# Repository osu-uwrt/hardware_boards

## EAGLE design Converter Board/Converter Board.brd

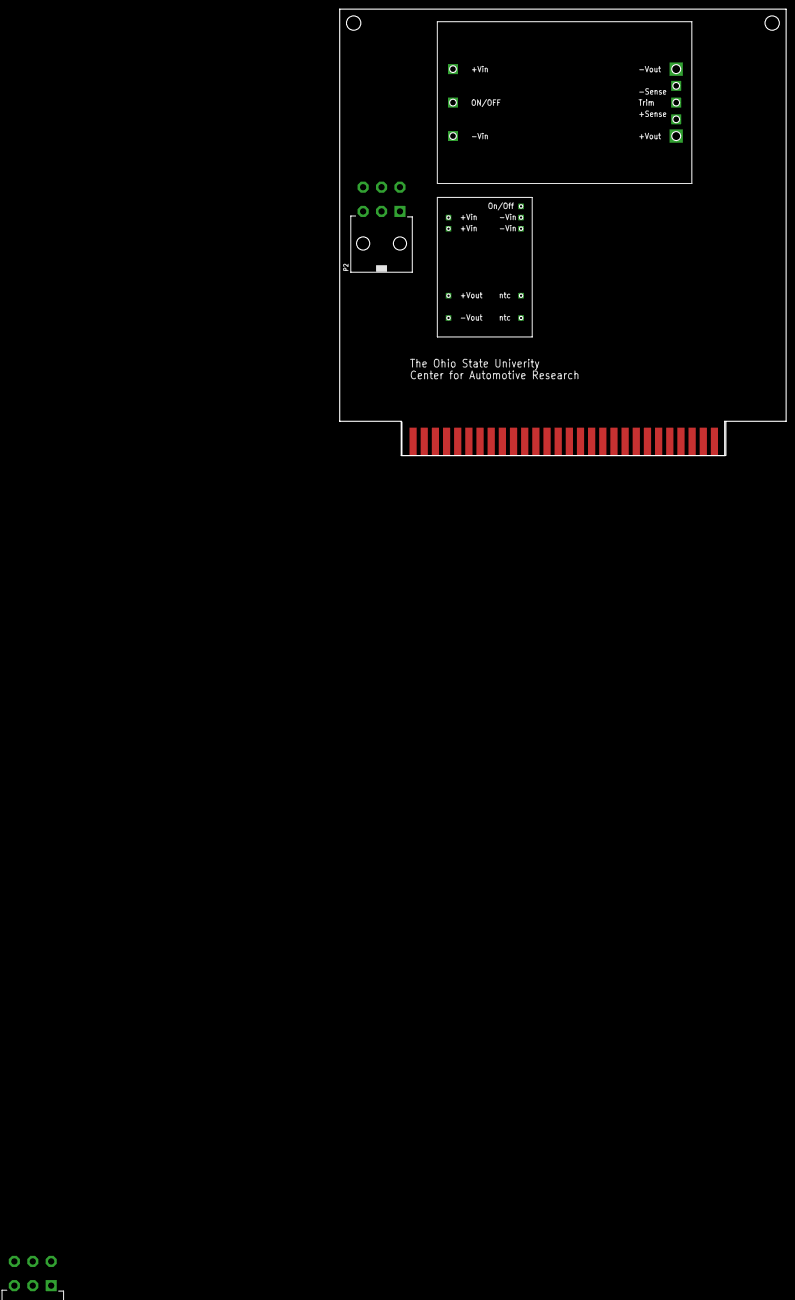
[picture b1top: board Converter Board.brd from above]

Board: 2 copper layers, 101.6 x 101.6 mm, 5 parts (0 on the bottom side), 6 nets, no tracks yet.

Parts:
P1, P2: 39-30-06?; 39-30-?06?
U$1: 3.3VCONV
U$2: 12VCONV
U$3: 5530843; 5530843-6-BOARDFINGERS

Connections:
unnamed: P2.4, P2.5, P2.6, U$1.22, U$1.23, U$2.1,+VIN
unnamed: P2.1, P2.2, P2.3, U$1.2, U$1.3, U$2.3,-VIN
unnamed: U$1.14, U$3.3.3VP1, U$3.3.3VP2, U$3.3.3VP3
unnamed: U$1.16, U$3.GND1, U$3.GND2, U$3.GND3
unnamed: P1.1, P1.2, P1.3, U$2.4,-VOUT
unnamed: P1.4, P1.5, P1.6, U$2.8,+VOUT

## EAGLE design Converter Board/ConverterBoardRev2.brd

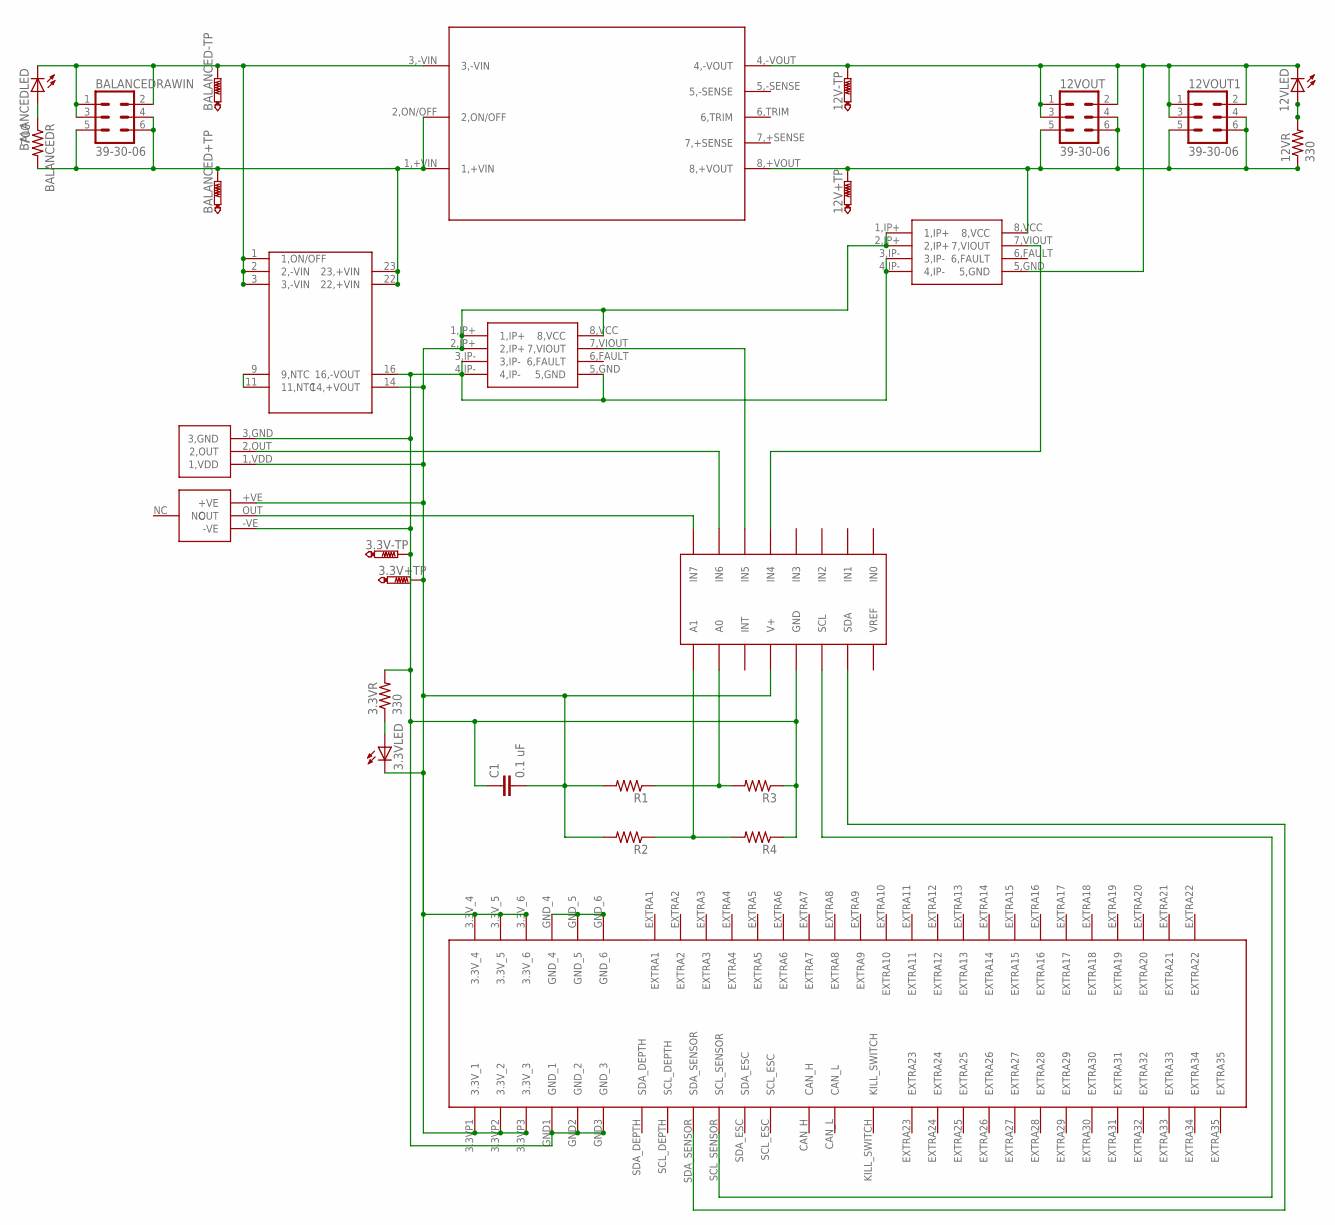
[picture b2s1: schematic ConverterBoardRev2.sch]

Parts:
3.3V+TP, 3.3V-TP, 12V+TP, 12V-TP: PTR1B1,27; B1,27
3.3VLED, 12VLED: LTST-S270GKT
3.3VR, 12VR: 330; 0204/7
12VOUT, 12VOUT1: 39-30-06; 39-30-?06?
BALANCED+TP: PTR1B1,27; B1,27
BALANCED-TP: PTR1B1,27; B1,27
BALANCEDLED: LTST-S270GKT
BALANCEDR: 700; 0204/7
BALANCEDRAWIN: 39-30-06; 39-30-?06?
C1: 0.1 uF; C025-024X044
R1, R2, R3, R4: R-US_0204/7; 0204/7
U$1: 12VCONV
U$2: 3.3VCONV
U$3: 5530843; 5530843-6-BOARDFINGERS
U$4, U$5: CURRENTSENS
U$6: HUMIDITYSENSOR
U$7: TEMPSENS
U$8: ADC128D818; TSSOP-16

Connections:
3.3V+: 3.3V+TP.TP, 3.3VLED.CATHODE (C), C1.2, R1.2, R2.2, U$2.14 (14,+VOUT), U$3.3.3VP1 (3.3V_1), U$3.3.3VP2 (3.3V_2), U$3.3.3VP3 (3.3V_3), U$3.3.3V_4, U$3.3.3V_5, U$3.3.3V_6, U$4.1,IP+, U$4.2,IP+, U$5.1,IP+, U$5.2,IP+, U$5.8,VCC, U$6.+VE, U$7.1,VDD, U$8.V+
3.3V-: 3.3V-TP.TP, 3.3VR.2, C1.1, R3.1, R4.1, U$2.16 (16,-VOUT), U$3.GND1 (GND_1), U$3.GND2 (GND_2), U$3.GND3 (GND_3), U$4.3,IP-, U$4.4,IP-, U$5.3,IP-, U$5.4,IP-, U$5.5,GND, U$6.-VE, U$7.3,GND, U$8.GND
3.3VLED: 3.3VLED.ANODE (A), 3.3VR.1
12V+: 12V+TP.TP, 12VOUT.4, 12VOUT.5, 12VOUT.6, 12VOUT1.4, 12VOUT1.5, 12VOUT1.6, 12VR.1, U$1.8,+VOUT, U$4.8,VCC
12V-: 12V-TP.TP, 12VLED.CATHODE (C), 12VOUT.1, 12VOUT.2, 12VOUT.3, 12VOUT1.1, 12VOUT1.2, 12VOUT1.3, U$1.4,-VOUT, U$4.5,GND
12VLED: 12VLED.ANODE (A), 12VR.2
BALANCED+: BALANCED+TP.TP, BALANCEDR.2, BALANCEDRAWIN.4, BALANCEDRAWIN.5, BALANCEDRAWIN.6, U$1.1,+VIN, U$1.2,ON/OFF, U$2.22 (22,+VIN), U$2.23 (23,+VIN)
BALANCED-: BALANCED-TP.TP, BALANCEDLED.CATHODE (C), BALANCEDRAWIN.1, BALANCEDRAWIN.2, BALANCEDRAWIN.3, U$1.3,-VIN, U$2.1 (1,ON/OFF), U$2.2 (2,-VIN), U$2.3 (3,-VIN)
BALANCEDLED: BALANCEDLED.ANODE (A), BALANCEDR.1
HUMIDITYDATA: U$6.OUT, U$8.IN7
unnamed: U$2.9 (9,NTC), U$2.11 (11,NTC)
unnamed: U$5.7,VIOUT, U$8.IN5
unnamed: U$4.7,VIOUT, U$8.IN4
unnamed: U$3.GND_4, U$3.GND_5, U$3.GND_6
unnamed: R1.1, R3.2, U$8.A0
unnamed: R2.1, R4.2, U$8.A1
unnamed: U$3.SCL_SENSOR, U$8.SCL
unnamed: U$3.SDA_SENSOR, U$8.SDA
TEMPDATA: U$7.2,OUT, U$8.IN6

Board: 2 copper layers, 28 parts (0 on the bottom side), 19 nets, no tracks yet.

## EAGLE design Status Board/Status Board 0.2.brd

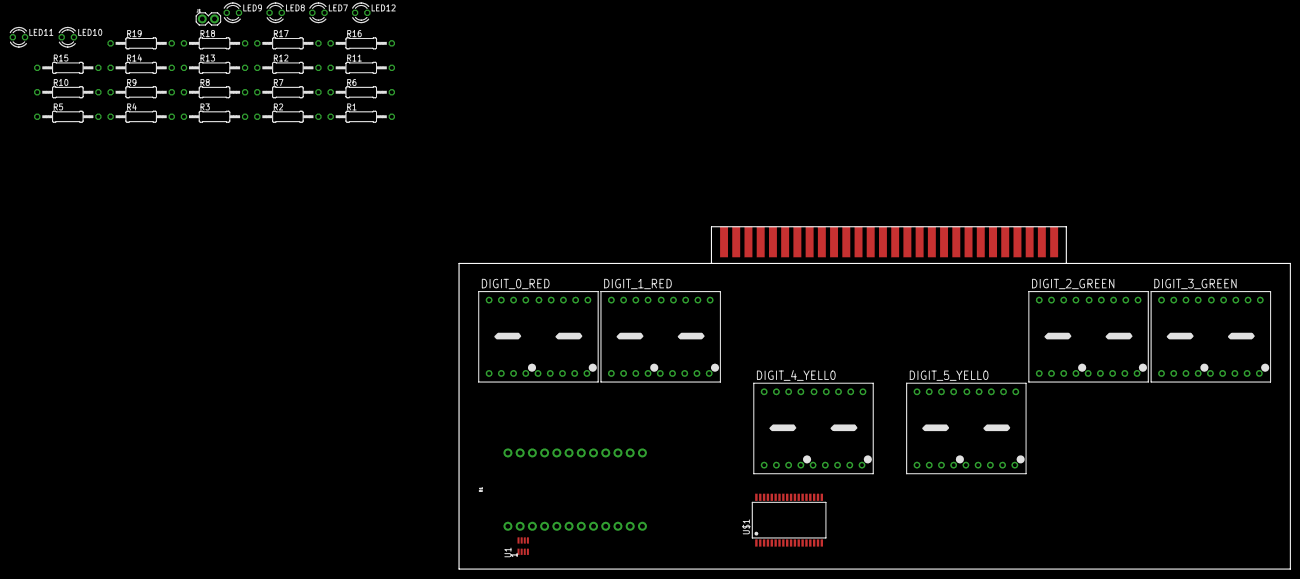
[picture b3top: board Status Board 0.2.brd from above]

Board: 2 copper layers, 172.7 x 71.1 mm, 36 parts (0 on the bottom side), 48 nets, no tracks yet.

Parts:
B1: SPARKFUN_PRO_MICRO
DIGIT_0_RED, DIGIT_1_RED: DC56-11SRWA; DA56
DIGIT_2_GREEN, DIGIT_3_GREEN: DC56-11GWA; DA56
DIGIT_4_YELL0, DIGIT_5_YELL0: DC56-11YWA; DA56
J1: 1X02
LED7, LED8, LED9, LED10, LED11, LED12: LED3MM
R1, R2, R3, R4, R5, R6, R7, R8, R9, R10, R11, R12, R13, R14, R15, R16, R17, R18, R19: 0207/12
U1: MAX3051ESA; 8-SOICN
U$1: MAX6954; SSOP36
U$2: 5530843; 5530843-6-BOARDFINGERS

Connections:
GND: B1.3, B1.4, B1.23, U1.2, U1.8, U$1.16, U$1.18, U$2.GND1, U$2.GND2, U$2.GND3, U$2.GND_4, U$2.GND_5, U$2.GND_6
unnamed: R2.2, U$1.8
unnamed: R3.2, U$1.9
unnamed: R4.2, U$1.10
unnamed: R5.2, U$1.11
unnamed: R6.2, U$1.12
unnamed: R7.2, U$1.13
unnamed: R8.2, U$1.14
unnamed: R9.2, U$1.15
unnamed: R10.2, U$1.22
unnamed: R11.2, U$1.23
unnamed: R12.2, U$1.24
unnamed: R13.2, U$1.25
unnamed: R14.2, U$1.26
unnamed: R15.2, U$1.27
unnamed: R16.2, U$1.28
unnamed: R17.2, U$1.29
unnamed: R18.2, U$1.30
unnamed: R19.2, U$1.31
unnamed: R1.2, U$1.7
unnamed: DIGIT_0_RED.13, DIGIT_0_RED.14, DIGIT_2_GREEN.16, DIGIT_3_GREEN.16, DIGIT_4_YELL0.16, DIGIT_5_YELL0.16, R1.1
unnamed: DIGIT_1_RED.13, DIGIT_1_RED.14, R2.1
unnamed: DIGIT_0_RED.16, DIGIT_1_RED.16, DIGIT_2_GREEN.13, DIGIT_2_GREEN.14, DIGIT_4_YELL0.15, DIGIT_5_YELL0.15, R3.1
unnamed: DIGIT_3_GREEN.13, DIGIT_3_GREEN.14, DIGIT_4_YELL0.3, DIGIT_5_YELL0.3, R4.1
unnamed: B1.14, U$1.6
unnamed: B1.15, U$1.4
unnamed: DIGIT_0_RED.15, DIGIT_1_RED.15, DIGIT_2_GREEN.15, DIGIT_3_GREEN.15, DIGIT_4_YELL0.13, DIGIT_4_YELL0.14, R5.1
unnamed: DIGIT_0_RED.3, DIGIT_1_RED.3, DIGIT_2_GREEN.3, DIGIT_3_GREEN.3, DIGIT_5_YELL0.13, DIGIT_5_YELL0.14, R6.1
unnamed: DIGIT_0_RED.1, DIGIT_1_RED.1, DIGIT_2_GREEN.1, DIGIT_3_GREEN.1, DIGIT_4_YELL0.1, DIGIT_5_YELL0.1, R9.1
unnamed: DIGIT_0_RED.18, DIGIT_1_RED.18, DIGIT_2_GREEN.18, DIGIT_3_GREEN.18, DIGIT_4_YELL0.18, DIGIT_5_YELL0.18, R10.1
unnamed: DIGIT_0_RED.17, DIGIT_1_RED.17, DIGIT_2_GREEN.17, DIGIT_3_GREEN.17, DIGIT_4_YELL0.17, DIGIT_5_YELL0.17, R11.1
unnamed: DIGIT_0_RED.11, DIGIT_1_RED.11, DIGIT_2_GREEN.11, DIGIT_3_GREEN.11, DIGIT_4_YELL0.11, DIGIT_5_YELL0.11, R12.1
unnamed: DIGIT_0_RED.10, DIGIT_1_RED.10, DIGIT_2_GREEN.10, DIGIT_3_GREEN.10, DIGIT_4_YELL0.10, DIGIT_5_YELL0.10, R13.1
unnamed: DIGIT_0_RED.2, DIGIT_1_RED.2, DIGIT_2_GREEN.2, DIGIT_3_GREEN.2, DIGIT_4_YELL0.2, DIGIT_5_YELL0.2, R7.1
unnamed: DIGIT_0_RED.6, DIGIT_1_RED.6, DIGIT_2_GREEN.6, DIGIT_3_GREEN.6, DIGIT_4_YELL0.6, DIGIT_5_YELL0.6, R15.1
unnamed: DIGIT_0_RED.5, DIGIT_1_RED.5, DIGIT_2_GREEN.5, DIGIT_3_GREEN.5, DIGIT_4_YELL0.5, DIGIT_5_YELL0.5, R16.1
unnamed: DIGIT_0_RED.12, DIGIT_1_RED.12, DIGIT_2_GREEN.12, DIGIT_3_GREEN.12, DIGIT_4_YELL0.12, DIGIT_5_YELL0.12, R17.1
unnamed: DIGIT_0_RED.7, DIGIT_1_RED.7, DIGIT_2_GREEN.7, DIGIT_3_GREEN.7, DIGIT_4_YELL0.7, DIGIT_5_YELL0.7, R18.1
unnamed: DIGIT_0_RED.9, DIGIT_1_RED.9, DIGIT_2_GREEN.9, DIGIT_3_GREEN.9, DIGIT_4_YELL0.9, DIGIT_5_YELL0.9, R19.1
unnamed: B1.16, U$1.5
unnamed: DIGIT_0_RED.8, DIGIT_1_RED.8, DIGIT_2_GREEN.8, DIGIT_3_GREEN.8, DIGIT_4_YELL0.8, DIGIT_5_YELL0.8, R14.1
unnamed: B1.13, U$1.3
unnamed: B1.6, U$2.SCL_ESC
unnamed: B1.5, U$2.SDA_ESC
unnamed: B1.1, U1.1
unnamed: B1.2, U1.4
unnamed: DIGIT_0_RED.4, DIGIT_1_RED.4, DIGIT_2_GREEN.4, DIGIT_3_GREEN.4, DIGIT_4_YELL0.4, DIGIT_5_YELL0.4, R8.1
VCC: B1.21, U1.3, U$1.19, U$1.21, U$2.3.3VP1, U$2.3.3VP2, U$2.3.3VP3, U$2.3.3V_4, U$2.3.3V_5, U$2.3.3V_6

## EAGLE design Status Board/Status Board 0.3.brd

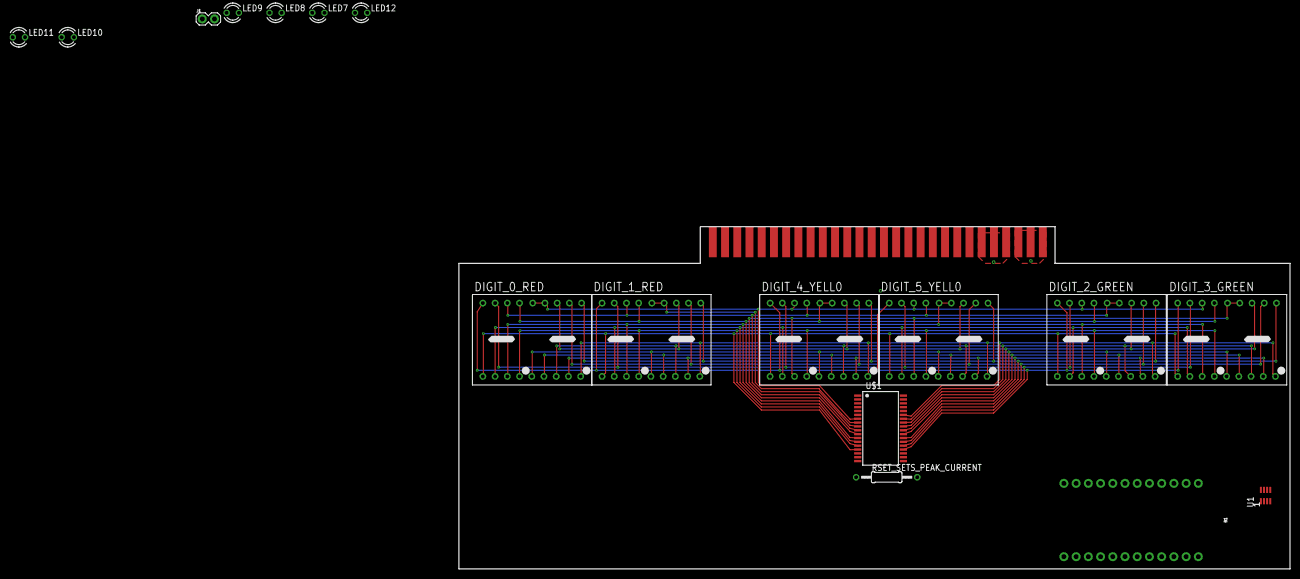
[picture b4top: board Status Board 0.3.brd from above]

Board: 2 copper layers, 172.7 x 71.1 mm, 18 parts (0 on the bottom side), 30 nets.

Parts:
B1: SPARKFUN_PRO_MICRO
DIGIT_0_RED, DIGIT_1_RED: DC56-11SRWA; DA56
DIGIT_2_GREEN, DIGIT_3_GREEN: DC56-11GWA; DA56
DIGIT_4_YELL0, DIGIT_5_YELL0: DC56-11YWA; DA56
J1: 1X02
LED7, LED8, LED9, LED10, LED11, LED12: LED3MM
RSET_SETS_PEAK_CURRENT: 0207/12
U1: MAX3051ESA; 8-SOICN
U$1: MAX6954; SSOP36
U$2: 5530843; 5530843-6-BOARDFINGERS

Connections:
GND: B1.3, B1.4, B1.23, RSET_SETS_PEAK_CURRENT.2, U1.2, U1.8, U$1.16, U$1.18, U$2.GND1, U$2.GND2, U$2.GND3, U$2.GND_4, U$2.GND_5, U$2.GND_6
unnamed: DIGIT_0_RED.13, DIGIT_0_RED.14, DIGIT_2_GREEN.16, DIGIT_3_GREEN.16, DIGIT_4_YELL0.16, DIGIT_5_YELL0.16, U$1.7
unnamed: DIGIT_1_RED.13, DIGIT_1_RED.14, U$1.8
unnamed: DIGIT_0_RED.16, DIGIT_1_RED.16, DIGIT_2_GREEN.13, DIGIT_2_GREEN.14, DIGIT_4_YELL0.15, DIGIT_5_YELL0.15, U$1.9
unnamed: DIGIT_3_GREEN.13, DIGIT_3_GREEN.14, DIGIT_4_YELL0.3, DIGIT_5_YELL0.3, U$1.10
unnamed: B1.14, U$1.6
unnamed: B1.15, U$1.4
unnamed: DIGIT_0_RED.15, DIGIT_1_RED.15, DIGIT_2_GREEN.15, DIGIT_3_GREEN.15, DIGIT_4_YELL0.13, DIGIT_4_YELL0.14, U$1.11
unnamed: DIGIT_0_RED.3, DIGIT_1_RED.3, DIGIT_2_GREEN.3, DIGIT_3_GREEN.3, DIGIT_5_YELL0.13, DIGIT_5_YELL0.14, U$1.12
unnamed: DIGIT_0_RED.1, DIGIT_1_RED.1, DIGIT_2_GREEN.1, DIGIT_3_GREEN.1, DIGIT_4_YELL0.1, DIGIT_5_YELL0.1, U$1.15
unnamed: DIGIT_0_RED.18, DIGIT_1_RED.18, DIGIT_2_GREEN.18, DIGIT_3_GREEN.18, DIGIT_4_YELL0.18, DIGIT_5_YELL0.18, U$1.22
unnamed: DIGIT_0_RED.17, DIGIT_1_RED.17, DIGIT_2_GREEN.17, DIGIT_3_GREEN.17, DIGIT_4_YELL0.17, DIGIT_5_YELL0.17, U$1.23
unnamed: DIGIT_0_RED.11, DIGIT_1_RED.11, DIGIT_2_GREEN.11, DIGIT_3_GREEN.11, DIGIT_4_YELL0.11, DIGIT_5_YELL0.11, U$1.24
unnamed: DIGIT_0_RED.10, DIGIT_1_RED.10, DIGIT_2_GREEN.10, DIGIT_3_GREEN.10, DIGIT_4_YELL0.10, DIGIT_5_YELL0.10, U$1.25
unnamed: DIGIT_0_RED.2, DIGIT_1_RED.2, DIGIT_2_GREEN.2, DIGIT_3_GREEN.2, DIGIT_4_YELL0.2, DIGIT_5_YELL0.2, U$1.13
unnamed: DIGIT_0_RED.6, DIGIT_1_RED.6, DIGIT_2_GREEN.6, DIGIT_3_GREEN.6, DIGIT_4_YELL0.6, DIGIT_5_YELL0.6, U$1.27
unnamed: DIGIT_0_RED.5, DIGIT_1_RED.5, DIGIT_2_GREEN.5, DIGIT_3_GREEN.5, DIGIT_4_YELL0.5, DIGIT_5_YELL0.5, U$1.28
unnamed: DIGIT_0_RED.12, DIGIT_1_RED.12, DIGIT_2_GREEN.12, DIGIT_3_GREEN.12, DIGIT_4_YELL0.12, DIGIT_5_YELL0.12, U$1.29
unnamed: DIGIT_0_RED.7, DIGIT_1_RED.7, DIGIT_2_GREEN.7, DIGIT_3_GREEN.7, DIGIT_4_YELL0.7, DIGIT_5_YELL0.7, U$1.30
unnamed: DIGIT_0_RED.9, DIGIT_1_RED.9, DIGIT_2_GREEN.9, DIGIT_3_GREEN.9, DIGIT_4_YELL0.9, DIGIT_5_YELL0.9, U$1.31
unnamed: B1.16, U$1.5
unnamed: DIGIT_0_RED.8, DIGIT_1_RED.8, DIGIT_2_GREEN.8, DIGIT_3_GREEN.8, DIGIT_4_YELL0.8, DIGIT_5_YELL0.8, U$1.26
unnamed: B1.13, U$1.3
unnamed: B1.6, U$2.SCL_ESC
unnamed: B1.5, U$2.SDA_ESC
unnamed: B1.1, U1.1
unnamed: B1.2, U1.4
unnamed: RSET_SETS_PEAK_CURRENT.1, U$1.17
unnamed: DIGIT_0_RED.4, DIGIT_1_RED.4, DIGIT_2_GREEN.4, DIGIT_3_GREEN.4, DIGIT_4_YELL0.4, DIGIT_5_YELL0.4, U$1.14
VCC: B1.21, U1.3, U$1.19, U$1.21, U$2.3.3VP1, U$2.3.3VP2, U$2.3.3VP3, U$2.3.3V_4, U$2.3.3V_5, U$2.3.3V_6

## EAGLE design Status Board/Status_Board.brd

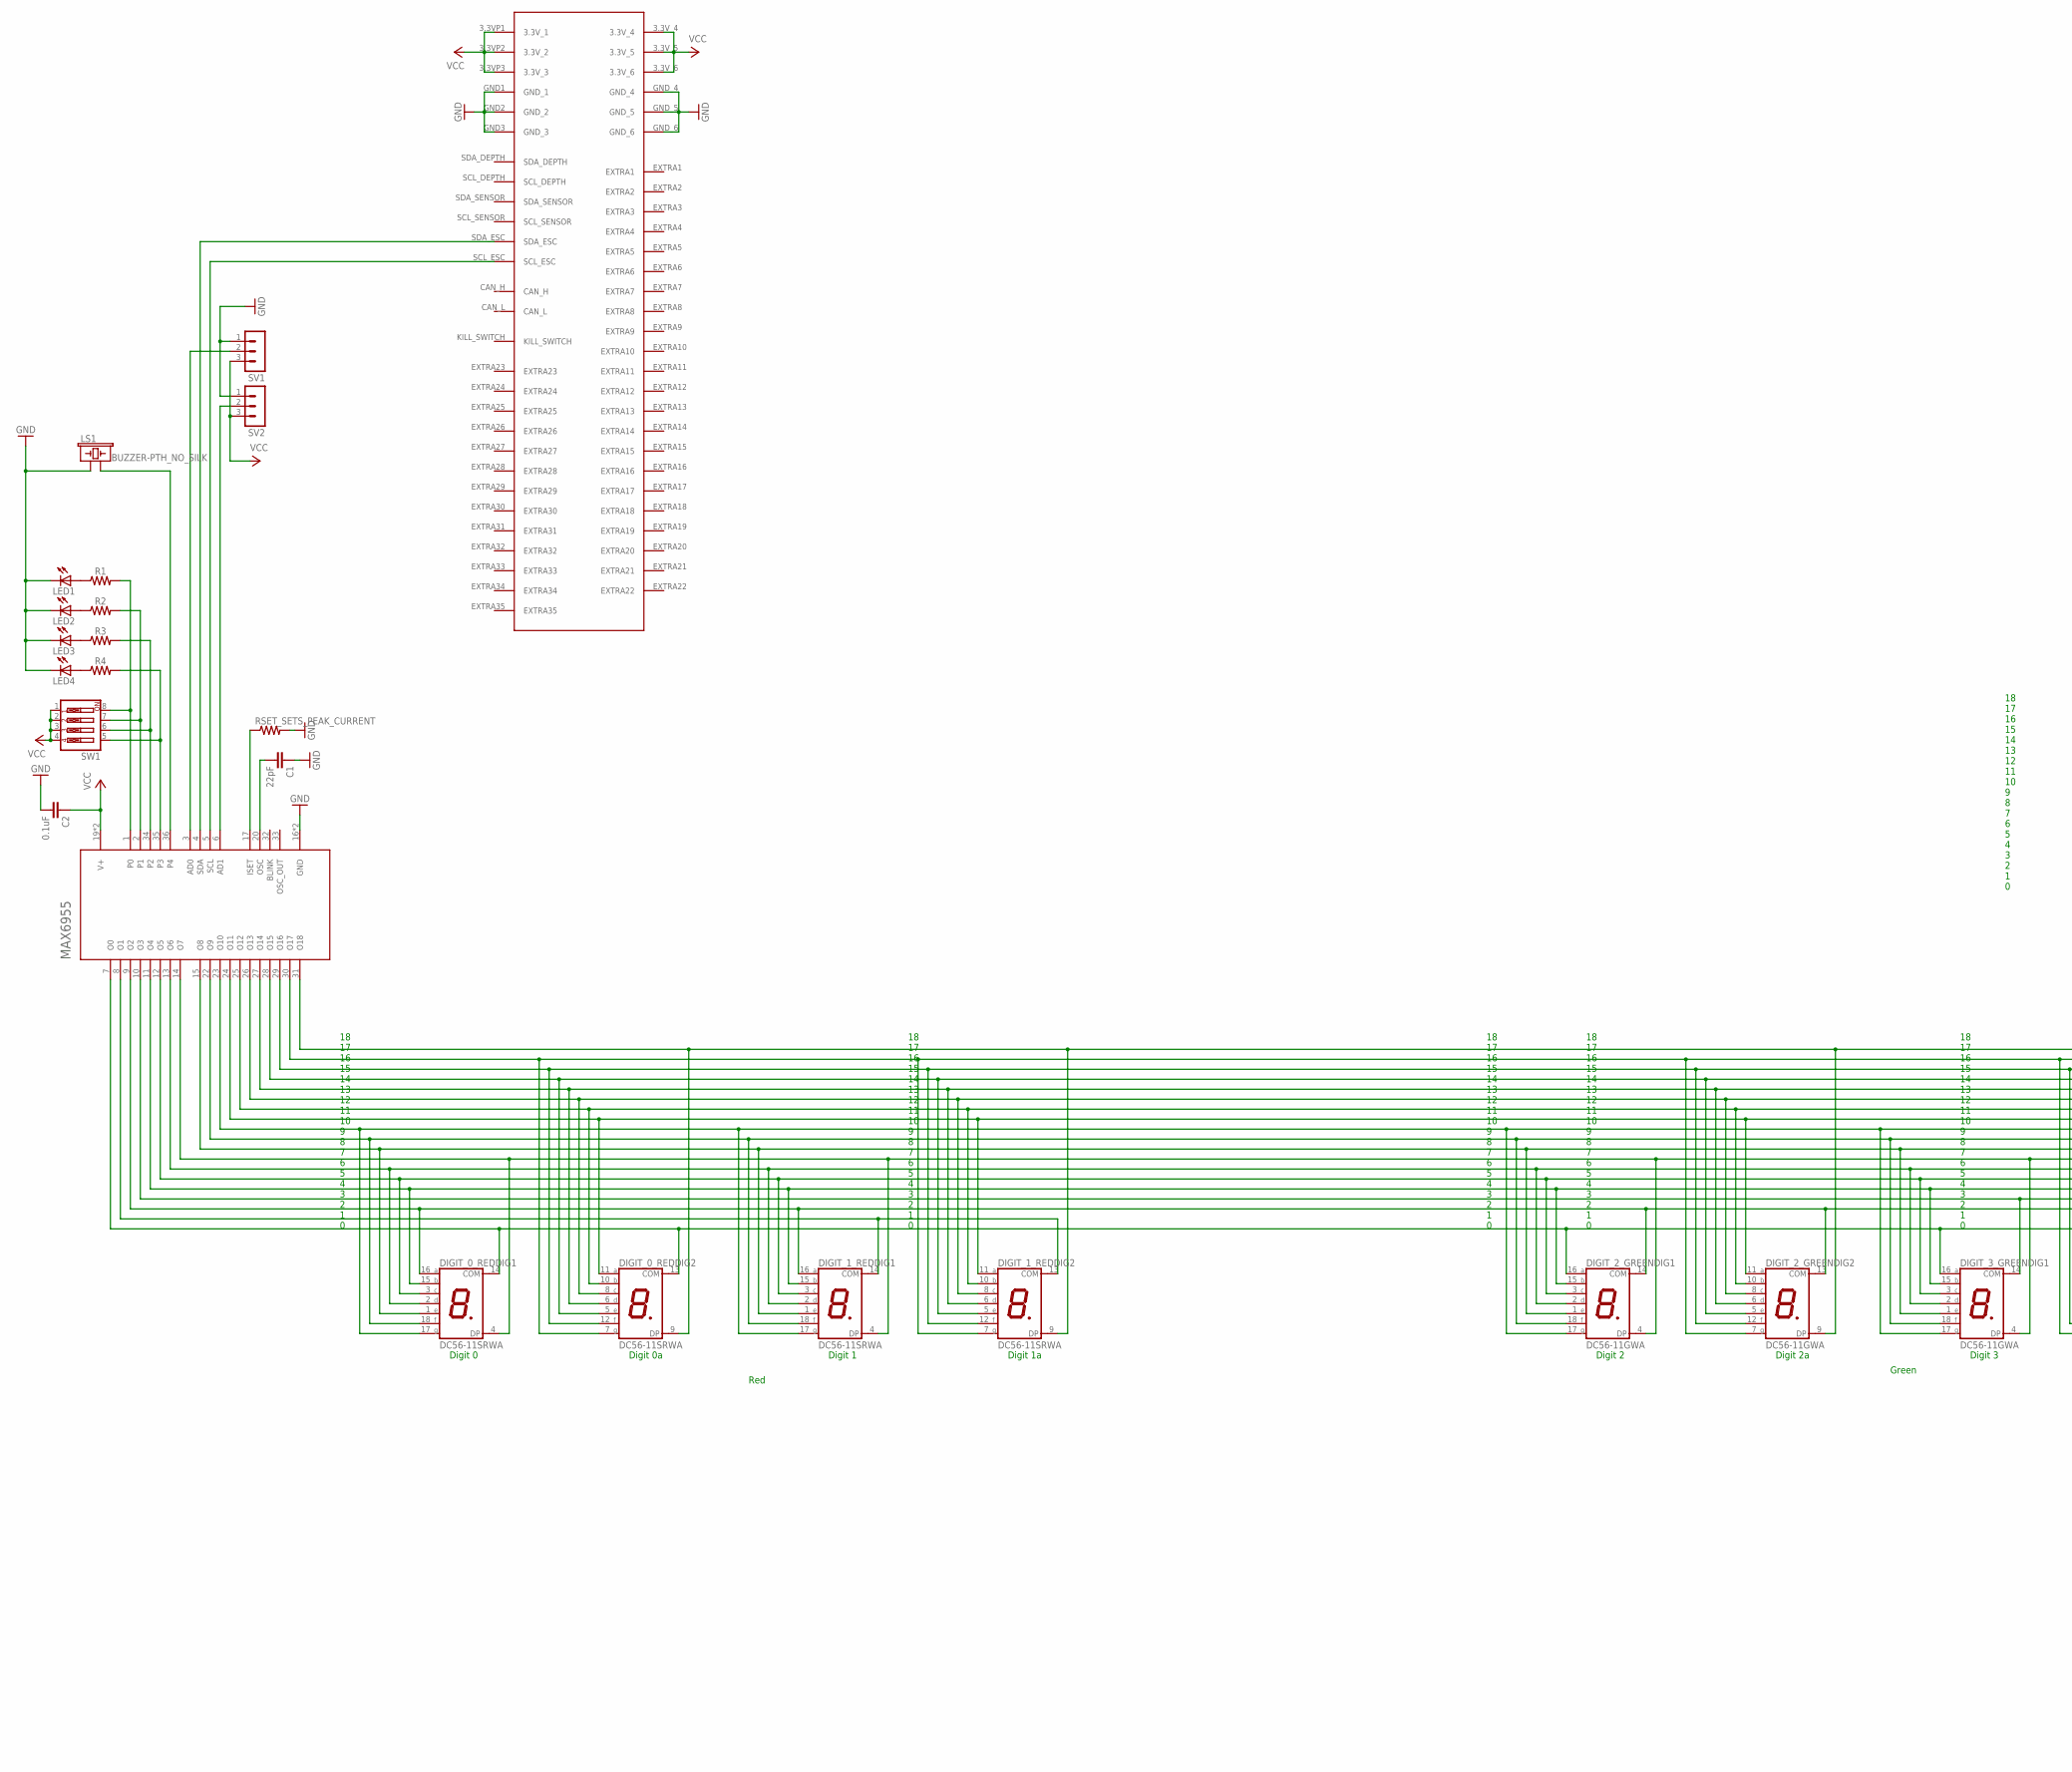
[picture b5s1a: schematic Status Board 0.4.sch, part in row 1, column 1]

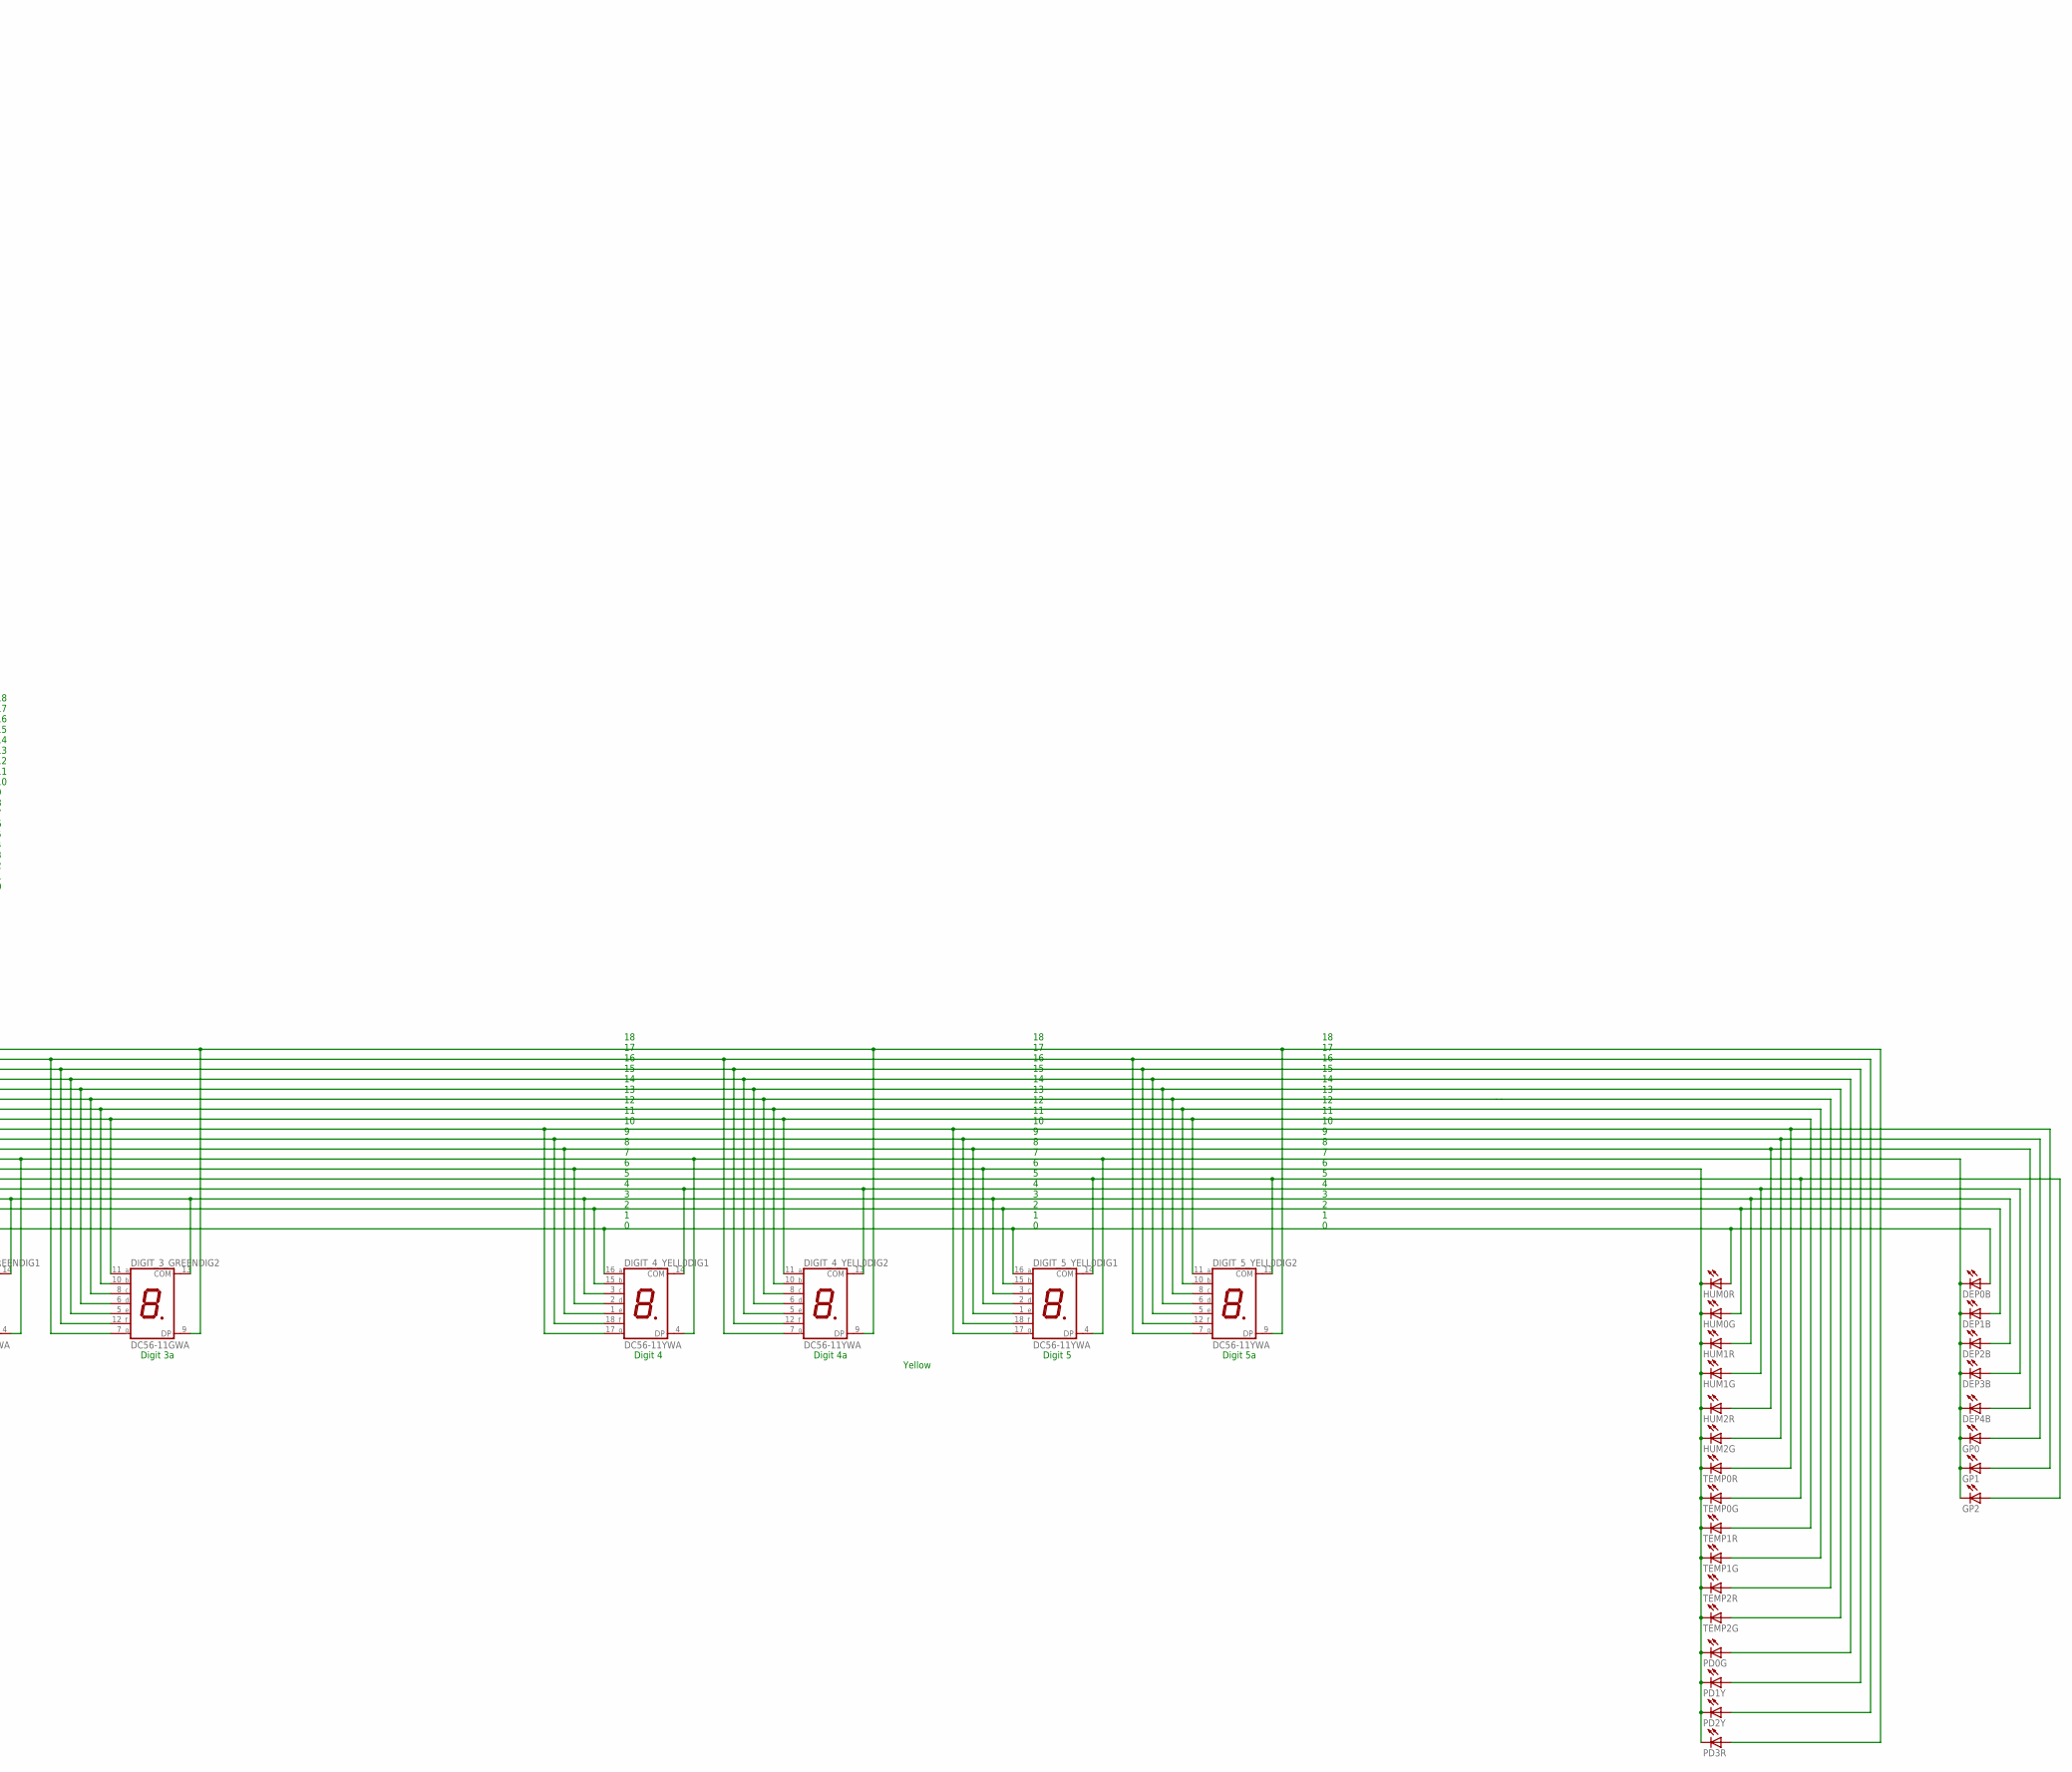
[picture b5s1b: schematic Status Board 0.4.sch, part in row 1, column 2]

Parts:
C1: 22pF; CAP-PTH-2.54
C2: 0.1uF; CAP-PTH-SMALL-KIT
DEP0B, DEP1B, DEP2B, DEP3B, DEP4B: LED3MM
DIGIT_0_RED, DIGIT_1_RED: DC56-11SRWA; DA56
DIGIT_2_GREEN, DIGIT_3_GREEN: DC56-11GWA; DA56
DIGIT_4_YELL0, DIGIT_5_YELL0: DC56-11YWA; DA56
GP0, GP1, GP2: LED3MM
HUM0G, HUM0R, HUM1G, HUM1R, HUM2G, HUM2R: LED3MM
LED1, LED2, LED3, LED4: LED_ESML0603; LED_SML0603
LS1: BUZZER-PTH_NO_SILK; BUZZER-12MM-NS
MAX6955: MAX6955; SSOP36
PD0G, PD1Y, PD2Y, PD3R: LED3MM
R1, R2, R3, R4: 68OHM-0603-1/10W-1%; 0603
RSET_SETS_PEAK_CURRENT: R-US_0207/12; 0207/12
SV1, SV2: MA03-1
SW1: SW_DIP-4; EDG-04
TEMP0G, TEMP0R, TEMP1G, TEMP1R, TEMP2G, TEMP2R: LED3MM
U$2: 5530843; 5530843-6-BOARDFINGERS

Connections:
013: DIGIT_0_RED.8 (C), DIGIT_1_RED.8 (C), DIGIT_2_GREEN.8 (C), DIGIT_3_GREEN.8 (C), DIGIT_4_YELL0.8 (C), DIGIT_5_YELL0.8 (C), MAX6955.26 (O13), TEMP2R.A
AD0: MAX6955.3 (AD0), SV1.2; also elsewhere on the board
AD1: MAX6955.6 (AD1), SV2.2; also elsewhere on the board
GND: C1.1, C2.2, LED1.C, LED2.C, LED3.C, LED4.C, LS1.+ (1), MAX6955.16 (GND), MAX6955.18 (GND), RSET_SETS_PEAK_CURRENT.2, SV1.1, SV2.1, U$2.GND1 (GND_1), U$2.GND2 (GND_2), U$2.GND3 (GND_3), U$2.GND_4, U$2.GND_5, U$2.GND_6; also elsewhere on the board
ISET: MAX6955.17 (ISET), RSET_SETS_PEAK_CURRENT.1; also elsewhere on the board
unnamed: LED1.A, R1.1
unnamed: LED2.A, R2.1
unnamed: LED3.A, R3.1
unnamed: LED4.A, R4.1
O0: DEP0B.A, DIGIT_0_RED.13 (COM), DIGIT_0_RED.14 (COM), DIGIT_2_GREEN.16 (A), DIGIT_3_GREEN.16 (A), DIGIT_4_YELL0.16 (A), DIGIT_5_YELL0.16 (A), HUM0R.A, MAX6955.7 (O0)
O1: DIGIT_1_RED.13 (COM), DIGIT_1_RED.14 (COM), MAX6955.8 (O1)
O2: DEP1B.A, DIGIT_0_RED.16 (A), DIGIT_1_RED.16 (A), DIGIT_2_GREEN.13 (COM), DIGIT_2_GREEN.14 (COM), DIGIT_4_YELL0.15 (B), DIGIT_5_YELL0.15 (B), HUM0G.A, MAX6955.9 (O2)
O3: DEP2B.A, DIGIT_3_GREEN.13 (COM), DIGIT_3_GREEN.14 (COM), DIGIT_4_YELL0.3 (C), DIGIT_5_YELL0.3 (C), HUM1R.A, MAX6955.10 (O3)
O4: DEP3B.A, DIGIT_0_RED.15 (B), DIGIT_1_RED.15 (B), DIGIT_2_GREEN.15 (B), DIGIT_3_GREEN.15 (B), DIGIT_4_YELL0.13 (COM), DIGIT_4_YELL0.14 (COM), HUM1G.A, MAX6955.11 (O4)
O5: DIGIT_0_RED.3 (C), DIGIT_1_RED.3 (C), DIGIT_2_GREEN.3 (C), DIGIT_3_GREEN.3 (C), DIGIT_5_YELL0.13 (COM), DIGIT_5_YELL0.14 (COM), GP2.A, MAX6955.12 (O5), TEMP0G.A
O6: DIGIT_0_RED.2 (D), DIGIT_1_RED.2 (D), DIGIT_2_GREEN.2 (D), DIGIT_3_GREEN.2 (D), DIGIT_4_YELL0.2 (D), DIGIT_5_YELL0.2 (D), HUM0G.K (C), HUM0R.K (C), HUM1G.K (C), HUM1R.K (C), HUM2G.K (C), HUM2R.K (C), MAX6955.13 (O6), PD0G.K (C), PD1Y.K (C), PD2Y.K (C), PD3R.K (C), TEMP0G.K (C), TEMP0R.K (C), TEMP1G.K (C), TEMP1R.K (C), TEMP2G.K (C), TEMP2R.K (C)
O7: DEP0B.K (C), DEP1B.K (C), DEP2B.K (C), DEP3B.K (C), DEP4B.K (C), DIGIT_0_RED.4 (DP), DIGIT_1_RED.4 (DP), DIGIT_2_GREEN.4 (DP), DIGIT_3_GREEN.4 (DP), DIGIT_4_YELL0.4 (DP), DIGIT_5_YELL0.4 (DP), GP0.K (C), GP1.K (C), GP2.K (C), MAX6955.14 (O7)
O8: DEP4B.A, DIGIT_0_RED.1 (E), DIGIT_1_RED.1 (E), DIGIT_2_GREEN.1 (E), DIGIT_3_GREEN.1 (E), DIGIT_4_YELL0.1 (E), DIGIT_5_YELL0.1 (E), HUM2R.A, MAX6955.15 (O8)
O9: DIGIT_0_RED.18 (F), DIGIT_1_RED.18 (F), DIGIT_2_GREEN.18 (F), DIGIT_3_GREEN.18 (F), DIGIT_4_YELL0.18 (F), DIGIT_5_YELL0.18 (F), GP0.A, HUM2G.A, MAX6955.22 (O9)
O10: DIGIT_0_RED.17 (G), DIGIT_1_RED.17 (G), DIGIT_2_GREEN.17 (G), DIGIT_3_GREEN.17 (G), DIGIT_4_YELL0.17 (G), DIGIT_5_YELL0.17 (G), GP1.A, MAX6955.23 (O10), TEMP0R.A
O11: DIGIT_0_RED.11 (A), DIGIT_1_RED.11 (A), DIGIT_2_GREEN.11 (A), DIGIT_3_GREEN.11 (A), DIGIT_4_YELL0.11 (A), DIGIT_5_YELL0.11 (A), MAX6955.24 (O11), TEMP1R.A
O12: DIGIT_0_RED.10 (B), DIGIT_1_RED.10 (B), DIGIT_2_GREEN.10 (B), DIGIT_3_GREEN.10 (B), DIGIT_4_YELL0.10 (B), DIGIT_5_YELL0.10 (B), MAX6955.25 (O12), TEMP1G.A
O14: DIGIT_0_RED.6 (D), DIGIT_1_RED.6 (D), DIGIT_2_GREEN.6 (D), DIGIT_3_GREEN.6 (D), DIGIT_4_YELL0.6 (D), DIGIT_5_YELL0.6 (D), MAX6955.27 (O14), TEMP2G.A
O15: DIGIT_0_RED.5 (E), DIGIT_1_RED.5 (E), DIGIT_2_GREEN.5 (E), DIGIT_3_GREEN.5 (E), DIGIT_4_YELL0.5 (E), DIGIT_5_YELL0.5 (E), MAX6955.28 (O15), PD0G.A
O16: DIGIT_0_RED.12 (F), DIGIT_1_RED.12 (F), DIGIT_2_GREEN.12 (F), DIGIT_3_GREEN.12 (F), DIGIT_4_YELL0.12 (F), DIGIT_5_YELL0.12 (F), MAX6955.29 (O16), PD1Y.A
O17: DIGIT_0_RED.7 (G), DIGIT_1_RED.7 (G), DIGIT_2_GREEN.7 (G), DIGIT_3_GREEN.7 (G), DIGIT_4_YELL0.7 (G), DIGIT_5_YELL0.7 (G), MAX6955.30 (O17), PD2Y.A
O18: DIGIT_0_RED.9 (DP), DIGIT_1_RED.9 (DP), DIGIT_2_GREEN.9 (DP), DIGIT_3_GREEN.9 (DP), DIGIT_4_YELL0.9 (DP), DIGIT_5_YELL0.9 (DP), MAX6955.31 (O18), PD3R.A
OSC: C1.2, MAX6955.20 (OSC)
P0: MAX6955.1 (P0), R1.2, SW1.8
P1: MAX6955.2 (P1), R2.2, SW1.7
P2: MAX6955.34 (P2), R3.2, SW1.6
P3: MAX6955.35 (P3), R4.2, SW1.5
P4: LS1.- (2), MAX6955.36 (P4)
SCL: MAX6955.5 (SCL), U$2.SCL_ESC
SDA: MAX6955.4 (SDA), U$2.SDA_ESC
VCC: C2.1, MAX6955.19 (V+), MAX6955.21 (V+), SV1.3, SV2.3, SW1.1, SW1.2, SW1.3, SW1.4, U$2.3.3VP1 (3.3V_1), U$2.3.3VP2 (3.3V_2), U$2.3.3VP3 (3.3V_3), U$2.3.3V_4, U$2.3.3V_5, U$2.3.3V_6; also elsewhere on the board

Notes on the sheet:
Green
Red
Yellow
Digit 0
Digit 0a
18 17 16 15 14 13 12 11 10 9 8 7 6 5 4 3 2 1 0
Digit 1
Digit 1a
Digit 2
Digit 2a
Digit 3
Digit 3a
Digit 4
Digit 4a
Digit 5
Digit 5a

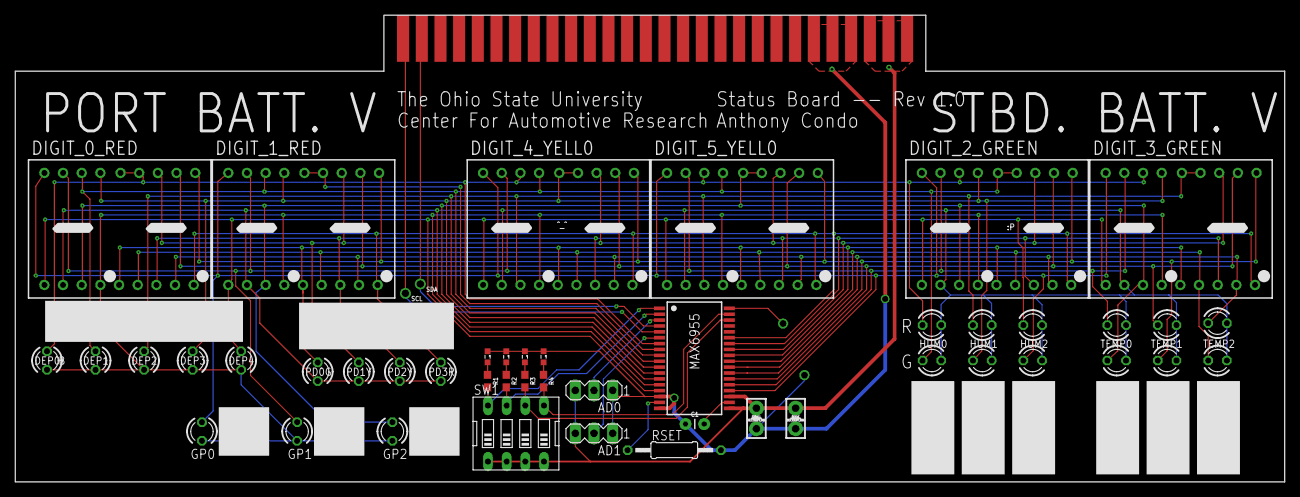
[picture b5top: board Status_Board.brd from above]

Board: 2 copper layers, 172.7 x 63.5 mm, 48 parts (0 on the bottom side), 36 nets.

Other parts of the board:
AD0, AD1: MA03-1
BULK: F; CAP-PTH-SMALL-KIT
RSET: 0207/12

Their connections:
AD0: AD0.2; also elsewhere on the board
AD1: AD1.2; also elsewhere on the board
GND: AD0.1, AD1.1, BULK.2, RSET.2; also elsewhere on the board
ISET: RSET.1; also elsewhere on the board
VCC: AD0.3, AD1.3, BULK.1; also elsewhere on the board

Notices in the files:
parts and their libraries:
con-molex-mini-fit: Copyright (C) 2011, Bob Starr
SparkFun-Boards: Licensing: Creative Commons ShareAlike 4.0 International - https://creativecommons.org/licenses/by-sa/4.0
